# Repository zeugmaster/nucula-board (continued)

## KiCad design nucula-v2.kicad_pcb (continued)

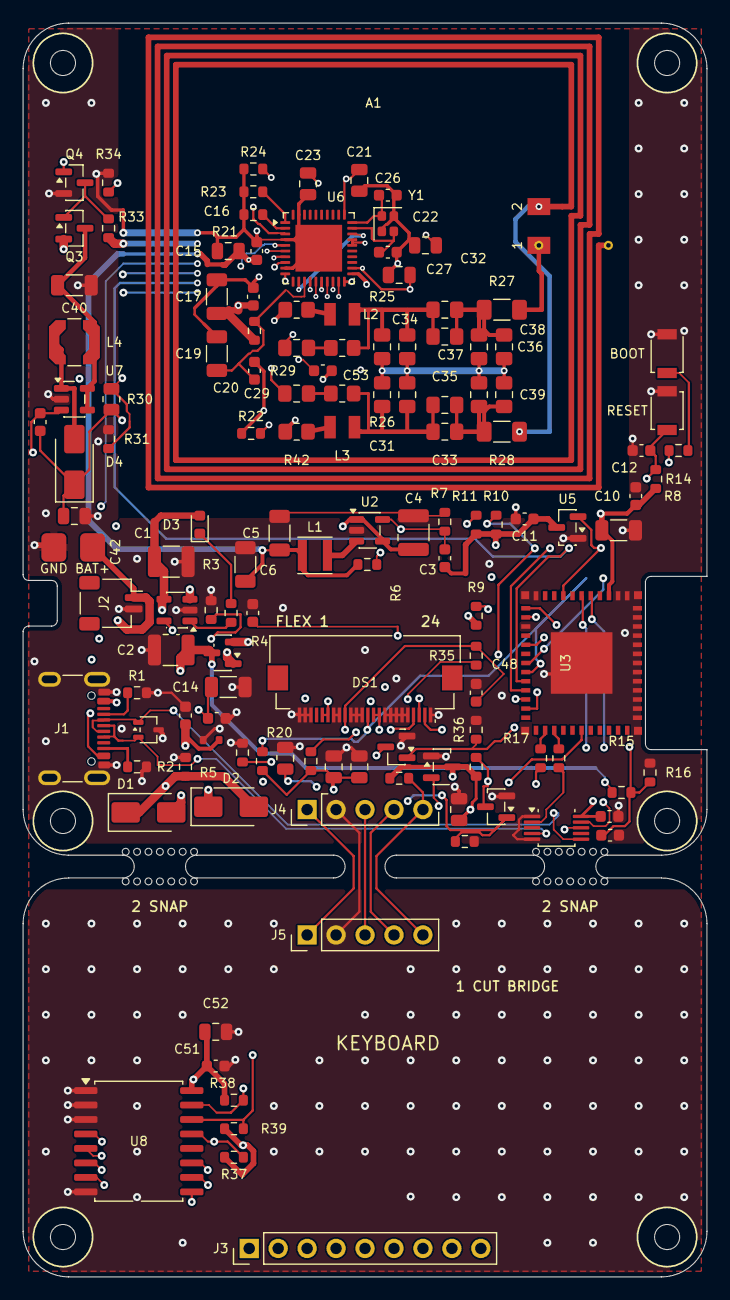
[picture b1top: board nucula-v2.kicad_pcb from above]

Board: 4 copper layers, 60.0 x 110.0 mm, 138 parts (0 on the bottom side), 72 nets.

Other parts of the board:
H1, H2, H3, H4, H5, H6: M2 2.2mm NPTH; MountingHole_2.2mm_M2_5.5mm_Keepout
MB1, MB2: MouseBite_2Rows7_D0.60_P1.00_Inset_Gap2.00

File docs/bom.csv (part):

Reference,Value,Footprint,Manufacturer,MPN,LCSC,Tolerance,Voltage,Rating,Dielectric,DNP,PCB Region,Status,Datasheet
C1,22uF,Capacitor_SMD:C_1210_3225Metric,Samsung Electro-Mechanics,CL32B226KAJNNNE,C309062,10%,25 V,,X7R,no,MAIN,SELECTED: manufacturer DC-bias curve checked; retain exact part or re-evaluate,https://product.samsungsem.com/mlcc/CL32B226KAJNNN.do
C2,22uF,Capacitor_SMD:C_1210_3225Metric,Samsung Electro-Mechanics,CL32B226KAJNNNE,C309062,10%,25 V,,X7R,no,MAIN,SELECTED: manufacturer DC-bias curve checked; retain exact part or re-evaluate,https://product.samsungsem.com/mlcc/CL32B226KAJNNN.do
C3,22pF,Capacitor_SMD:C_0603_1608Metric,Samsung Electro-Mechanics,CL10C220JB8NNNC,C1653,5%,50 V,,C0G,no,MAIN,,https://www.lcsc.com/datasheet/lcsc_datasheet_2304140030_Sam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
C4,22uF,Capacitor_SMD:C_1210_3225Metric,Samsung Electro-Mechanics,CL32B226KAJNNNE,C309062,10%,25 V,,X7R,no,MAIN,SELECTED: manufacturer DC-bias curve checked; retain exact part or re-evaluate,https://product.samsungsem.com/mlcc/CL32B226KAJNNN.do
C5,22uF,Capacitor_SMD:C_1206_3216Metric,Samsung Electro-Mechanics,CL31A226KAHNNNE,C12891,10%,25 V,,X5R,no,MAIN,SELECTED: manufacturer DC-bias curve checked,https://product.samsungsem.com/mlcc/CL31A226KAHNNN.do
C6,22uF,Capacitor_SMD:C_1206_3216Metric,Samsung Electro-Mechanics,CL31A226KAHNNNE,C12891,10%,25 V,,X5R,no,MAIN,SELECTED: manufacturer DC-bias curve checked,https://product.samsungsem.com/mlcc/CL31A226KAHNNN.do
C9,22uF,Capacitor_SMD:C_1206_3216Metric,Samsung Electro-Mechanics,CL31A226KAHNNNE,C12891,10%,25 V,,X5R,no,MAIN,SELECTED: manufacturer DC-bias curve checked,https://product.samsungsem.com/mlcc/CL31A226KAHNNN.do
C10,100nF,Capacitor_SMD:C_0603_1608Metric,Samsung Electro-Mechanics,CL10B104KB8NNNC,C1591,10%,50 V,,X7R,no,MAIN,,https://www.lcsc.com/datasheet/lcsc_datasheet_2304140030_Sam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
C11,100nF,Capacitor_SMD:C_0603_1608Metric,Samsung Electro-Mechanics,CL10B104KB8NNNC,C1591,10%,50 V,,X7R,no,MAIN,,https://www.lcsc.com/datasheet/lcsc_datasheet_2304140030_Sam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
C12,1uF,Capacitor_SMD:C_0603_1608Metric,Samsung Electro-Mechanics,CL10B105KA8NNNC,C29936,10%,25 V,,X7R,no,MAIN,,https://www.lcsc.com/datasheet/lcsc_datasheet_2304140030_Sam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
C13,100nF,Capacitor_SMD:C_0603_1608Metric,Samsung Electro-Mechanics,CL10B104KB8NNNC,C1591,10%,50 V,,X7R,no,MAIN,,https://www.lcsc.com/datasheet/lcsc_datasheet_2304140030_Sam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
C14,100nF,Capacitor_SMD:C_0603_1608Metric,Samsung Electro-Mechanics,CL10B104KB8NNNC,C1591,10%,50 V,,X7R,no,MAIN,,https://www.lcsc.com/datasheet/lcsc_datasheet_2304140030_Sam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
C15,1uF,Capacitor_SMD:C_0805_2012Metric,Samsung Electro-Mechanics,CL21B105KBFNNNE,C28323,10%,50 V,,X7R,no,MAIN,,https://product.samsungsem.com/mlcc/CL21B105KBFNNN.do
C16,100nF,Capacitor_SMD:C_0603_1608Metric,Samsung Electro-Mechanics,CL10B104KB8NNNC,C1591,10%,50 V,,X7R,no,MAIN,,https://product.samsungsem.com/mlcc/CL10B104KB8NNN.do
C17,10uF,Capacitor_SMD:C_1206_3216Metric,Samsung Electro-Mechanics,CL31B106KAHNNNE,C14860,10%,25 V,,X7R,no,MAIN,,https://product.samsungsem.com/mlcc/CL31B106KAHNNN.do
C18,100nF,Capacitor_SMD:C_0603_1608Metric,Samsung Electro-Mechanics,CL10B104KB8NNNC,C1591,10%,50 V,,X7R,no,MAIN,,https://product.samsungsem.com/mlcc/CL10B104KB8NNN.do
C19,10uF,Capacitor_SMD:C_1206_3216Metric,Samsung Electro-Mechanics,CL31B106KAHNNNE,C14860,10%,25 V,,X7R,no,MAIN,,https://product.samsungsem.com/mlcc/CL31B106KAHNNN.do
C20,100nF,Capacitor_SMD:C_0603_1608Metric,Samsung Electro-Mechanics,CL10B104KB8NNNC,C1591,10%,50 V,,X7R,no,MAIN,,https://product.samsungsem.com/mlcc/CL10B104KB8NNN.do
C21,2.2uF,Capacitor_SMD:C_0805_2012Metric,Samsung Electro-Mechanics,CL21B225KAFNNNE,C19110,10%,25 V,,X7R,no,MAIN,PN7160 AN12988 local decoupling; selected stocked prototype part is NRND; do not substitute without checking bias,https://product.samsungsem.com/mlcc/CL21B225KAFNNN.do
C22,2.2uF,Capacitor_SMD:C_0805_2012Metric,Samsung Electro-Mechanics,CL21B225KAFNNNE,C19110,10%,25 V,,X7R,no,MAIN,PN7160 AN12988 local decoupling; selected stocked prototype part is NRND; do not substitute without checking bias,https://product.samsungsem.com/mlcc/CL21B225KAFNNN.do
C23,2.2uF,Capacitor_SMD:C_0805_2012Metric,Samsung Electro-Mechanics,CL21B225KAFNNNE,C19110,10%,25 V,,X7R,no,MAIN,PN7160 AN12988 local decoupling; selected stocked prototype part is NRND; do not substitute without checking bias,https://product.samsungsem.com/mlcc/CL21B225KAFNNN.do
C24,2.2uF,Capacitor_SMD:C_0805_2012Metric,Samsung Electro-Mechanics,CL21B225KAFNNNE,C19110,10%,25 V,,X7R,no,MAIN,PN7160 AN12988 local decoupling; selected stocked prototype part is NRND; do not substitute without checking bias,https://product.samsungsem.com/mlcc/CL21B225KAFNNN.do
C25,100nF,Capacitor_SMD:C_0603_1608Metric,Samsung Electro-Mechanics,CL10B104KB8NNNC,C1591,10%,50 V,,X7R,no,MAIN,,https://product.samsungsem.com/mlcc/CL10B104KB8NNN.do
C26,12pF,Capacitor_SMD:C_0603_1608Metric,Samsung Electro-Mechanics,CL10C120JB8NNNC,C38523,5%,50 V,,C0G,no,MAIN,PROTOTYPE START: 12pF/15pF pair; tune carrier to -5..0ppm per AN14518,https://product.samsungsem.com/mlcc/CL10C120JB8NNN.do
C27,15pF,Capacitor_SMD:C_0603_1608Metric,Samsung Electro-Mechanics,CL10C150JB8NNNC,C1644,5%,50 V,,C0G,no,MAIN,PROTOTYPE START: 12pF/15pF pair; tune carrier to -5..0ppm per AN14518,https://product.samsungsem.com/mlcc/CL10C150JB8NNN.do
C28,1nF,Capacitor_SMD:C_0805_2012Metric_Pad1.18x1.45mm_HandSolder,Murata Electronics,GRM2165C2A102JA01D,C162289,5%,100 V,,C0G/NP0,no,MAIN,PROTOTYPE START: validate with VNA / AGC / RF stress measurements,https://www.lcsc.com/datasheet/lcsc_datasheet_2304140030_Mur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
C29,1nF,Capacitor_SMD:C_0805_2012Metric_Pad1.18x1.45mm_HandSolder,Murata Electronics,GRM2165C2A102JA01D,C162289,5%,100 V,,C0G/NP0,no,MAIN,PROTOTYPE START: validate with VNA / AGC / RF stress measurements,https://www.lcsc.com/datasheet/lcsc_datasheet_2304140030_Mur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
C30,330pF,Capacitor_SMD:C_0805_2012Metric_Pad1.18x1.45mm_HandSolder,YAGEO,CC0805FRNPO0BN331,C527075,1%,100 V,,C0G/NP0,no,MAIN,PROTOTYPE: 330pF 1% + 33pF 5% in parallel = 363pF +/-1.364%; fit symmetrically; measure and retune,https://wmsc.lcsc.com/wmsc/upload/file/pdf/v2/lcsc/200526183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
C31,330pF,Capacitor_SMD:C_0805_2012Metric_Pad1.18x1.45mm_HandSolder,YAGEO,CC0805FRNPO0BN331,C527075,1%,100 V,,C0G/NP0,no,MAIN,PROTOTYPE: 330pF 1% + 33pF 5% in parallel = 363pF +/-1.364%; fit symmetrically; measure and retune,https://wmsc.lcsc.com/wmsc/upload/file/pdf/v2/lcsc/200526183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
C32,68pF,Capacitor_SMD:C_0805_2012Metric_Pad1.18x1.45mm_HandSolder,YAGEO,CC0805FRNPO0BN680,C576904,1%,100 V,,C0G/NP0,no,MAIN,PROTOTYPE START: validate with VNA / AGC / RF stress measurements,https://wmsc.lcsc.com/wmsc/upload/file/pdf/v2/lcsc/221209103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
C33,68pF,Capacitor_SMD:C_0805_2012Metric_Pad1.18x1.45mm_HandSolder,YAGEO,CC0805FRNPO0BN680,C576904,1%,100 V,,C0G/NP0,no,MAIN,PROTOTYPE START: validate with VNA / AGC / RF stress measurements,https://wmsc.lcsc.com/wmsc/upload/file/pdf/v2/lcsc/221209103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
C34,DNP / TRIM,Nucula_Project:C_0805_HandSolder_NoPaste,,,,<=2% or +/-0.1pF for small trims,100 V,,C0G/NP0,yes,MAIN,DNP: fit equal pairs; 0.5-22pF typical fine trim,
C35,DNP / TRIM,Nucula_Project:C_0805_HandSolder_NoPaste,,,,<=2% or +/-0.1pF for small trims,100 V,,C0G/NP0,yes,MAIN,DNP: fit equal pairs; 0.5-22pF typical fine trim,
C36,100pF,Capacitor_SMD:C_0805_2012Metric_Pad1.18x1.45mm_HandSolder,YAGEO,CC0805GRNPO0BN101,C527192,2%,100 V,,C0G/NP0,no,MAIN,PROTOTYPE START: validate with VNA / AGC / RF stress measurements,https://wmsc.lcsc.com/wmsc/upload/file/pdf/v2/lcsc/200522213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
C37,100pF,Capacitor_SMD:C_0805_2012Metric_Pad1.18x1.45mm_HandSolder,YAGEO,CC0805GRNPO0BN101,C527192,2%,100 V,,C0G/NP0,no,MAIN,PROTOTYPE START: validate with VNA / AGC / RF stress measurements,https://wmsc.lcsc.com/wmsc/upload/file/pdf/v2/lcsc/200522213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
C38,DNP / TRIM,Nucula_Project:C_0805_HandSolder_NoPaste,,,,<=2% or +/-0.1pF for small trims,100 V,,C0G/NP0,yes,MAIN,DNP: fit equal pairs; 0.5-22pF typical fine trim,
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
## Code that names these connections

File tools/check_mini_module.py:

#!/usr/bin/env python3
"""Check MINI-1 datasheet pins, flush antenna fit, keepout and USB fanout.

Run with KiCad's pcbnew-enabled Python, after schematic export and zone refill.
This does not qualify RF performance, firmware, assembly or physical tolerances.
"""
import argparse
import hashlib
import json
from pathlib import Path
import xml.etree.ElementTree as ET
import pcbnew as k
from check_pcb_layout import rectangle, overlap_area

ROOT = Path(__file__).resolve().parents[1]
MPN = 'ESP32-C3-MINI-1-H4X'
FOOTPRINT = 'Nucula_Project:' + MPN + '_NoEPADSolder'
# Espressif MINI-1 datasheet v2.2, Table 3-1, independent of schematic symbol.
SIGNALS = {
    '3': '+3V3', '5': 'STRAP_GPIO2', '6': 'OLED_PWR_EN', '8': 'ESP_EN',
    '12': 'VBAT_ADC', '13': 'USB_PRESENT_N', '16': 'OLED_RESET',
    '18': 'I2C_SDA', '19': 'I2C_SCL', '20': 'NFC_IRQ', '21': 'NFC_VEN',
    '22': 'STRAP_GPIO8', '23': 'BOOT_N', '26': 'Net-(U3-IO18)',
    '27': 'Net-(U3-IO19)', '30': 'KEY_INT_N',
}
GROUND = {str(n) for n in [1, 2, 11, 14, *range(36, 54)]}
NC = {str(n) for n in [4, 7, 9, 10, 15, 17, 24, 25, 28, 29, 32, 33, 34, 35]}


def audit(board_path, netlist_path):
    board = k.LoadBoard(str(board_path))
    fps = {f.GetReference(): f for f in board.GetFootprints()}
    fp = fps['U3']
    pads = {p.GetNumber(): p for p in fp.Pads()}
    xml = ET.parse(netlist_path)
    nets = {n.get('name'): {(p.get('ref'), p.get('pin')) for p in n.findall('node')}
            for n in xml.findall('./nets/net')}
    pin = {p: n for n, members in nets.items() for p in members}
    comp = next(c for c in xml.findall('./components/comp') if c.get('ref') == 'U3')
    checks = {}
    checks['selected_4MB_H4X_module_and_footprint'] = (
        fp.GetValue() == comp.findtext('value') == MPN
        and str(fp.GetFPIDAsString()) == comp.findtext('footprint') == FOOTPRINT
        and fp.GetFieldText('MPN') == MPN and fp.GetFieldText('LCSC') == 'C41349510')
    checks['all_53_module_pins_present'] = set(pads) == {str(n) for n in range(1, 54)}
    checks['datasheet_signals_preserve_GPIO_assignments'] = all(
        pin.get(('U3', number), '').rsplit('/', 1)[-1] == name
        for number, name in SIGNALS.items())
    checks['all_22_ground_pins_grounded'] = all(pin.get(('U3', n)) == 'GND' for n in GROUND)
    checks['NC_pins_and_reserved_GPIO21_isolated'] = all(
        pin.get(('U3', n), '').startswith('unconnected-')
        and nets[pin['U3', n]] == {('U3', n)} for n in NC | {'31'})
    checks['every_PCB_pad_matches_schematic'] = all(
        p.GetNetname().replace('{slash}', '/') == pin.get(('U3', n)) for n, p in pads.items())
    epad = pads['49']
    checks['optional_EPAD_joint_omitted_without_via_in_pad'] = (
        not epad.IsOnLayer(k.F_Mask) and not epad.IsOnLayer(k.F_Paste)
        and epad.GetDrillSize().x == 0 and epad.GetNetname() == 'GND')
    checks['all_perimeter_pads_have_mask_and_paste'] = all(
        p.IsOnLayer(k.F_Mask) and p.IsOnLayer(k.F_Paste) for n, p in pads.items() if n != '49')
    position = [k.ToMM(fp.GetPosition().x), k.ToMM(fp.GetPosition().y), fp.GetOrientationDegrees()]
    checks['module_position_locked'] = position == [101.7, 106.14, -90.0] and fp.IsLocked()
    # Antenna is local x +/-6.6, y -8.3..-2.9, at the above rotation.
    antenna = rectangle([104.6, 99.54, 110.0, 112.74])
    outline = k.SHAPE_POLY_SET()
    checks['outline_is_closed'] = board.GetBoardPolygonOutlines(outline, False)
    checks['antenna_has_no_baseboard_underneath'] = overlap_area(outline, antenna) < 1e-7
    checks['antenna_tip_flush_with_110mm_board_edge'] = (
        abs(position[0] + 8.3 - 110) < 1e-9 and abs(k.ToMM(outline.BBox().GetRight()) - 110) < 1e-5)
    rules = [z for z in fp.Zones() if z.GetIsRuleArea()]
    checks['antenna_keepout_matches_datasheet_on_all_four_layers'] = len(rules) == 1 and all(
        all(z.IsOnLayer(l) for l in [k.F_Cu, k.In1_Cu, k.In2_Cu, k.B_Cu])
        and z.GetDoNotAllowTracks() and z.GetDoNotAllowVias() and z.GetDoNotAllowPads()
        and z.GetDoNotAllowZoneFills() and abs(overlap_area(z.Outline(), antenna) - 5.4 * 13.2) < 1e-7
        for z in rules)
    checks['no_filled_copper_under_antenna'] = all(
        overlap_area(z.GetFilledPolysList(layer), antenna) < 1e-7
        for z in board.Zones() if not z.GetIsRuleArea()
        for layer in [k.F_Cu, k.In1_Cu, k.In2_Cu, k.B_Cu] if z.IsOnLayer(layer))
    lengths = {}
    for gpio in ['18', '19']:
        net = f'Net-(U3-IO{gpio})'
        tracks = [t for t in board.GetTracks() if t.GetNetname() == net]
        checks[f'USB_GPIO{gpio}_has_no_vias_and_stays_on_front'] = all(
            not isinstance(t, k.PCB_VIA) and t.GetLayer() == k.F_Cu for t in tracks) and bool(tracks)
        lengths[gpio] = sum(k.ToMM(t.GetLength()) for t in tracks)
    checks['USB_module_to_resistor_lengths_match_within_0_01mm'] = abs(lengths['18'] - lengths['19']) < .01
    return dict(passed=all(checks.values()), checks=checks, selected_module=MPN,
                module_body_mm=[13.2, 16.6, 2.4], module_position=position,
                antenna_bounds_mm=[104.6, 99.54, 110, 112.74],
                notch_bounds_mm=[104.6, 98.54, 110, 113.74], notch_internal_radius_mm=.5,
                USB_module_to_resistor_lengths_mm=lengths,
                board_sha256=hashlib.sha256(board_path.read_bytes()).hexdigest(),
                netlist_sha256=hashlib.sha256(netlist_path.read_bytes()).hexdigest(), hardware_tested=False)


if __name__ == '__main__':
    ap = argparse.ArgumentParser(description=__doc__)
    ap.add_argument('--board', type=Path, default=ROOT/'nucula-v2.kicad_pcb')
    ap.add_argument('--netlist', type=Path, default=ROOT/'docs/netlist.xml')
    ap.add_argument('--out', type=Path, default=ROOT/'docs/pcb/mini-module-check.json')
    args = ap.parse_args()
    result = audit(args.board, args.netlist)
    args.out.write_text(json.dumps(result, indent=2)+'\n')
    for name, ok in result['checks'].items():
        print(('PASS ' if ok else 'FAIL ')+name)
    raise SystemExit(0 if result['passed'] else 1)
